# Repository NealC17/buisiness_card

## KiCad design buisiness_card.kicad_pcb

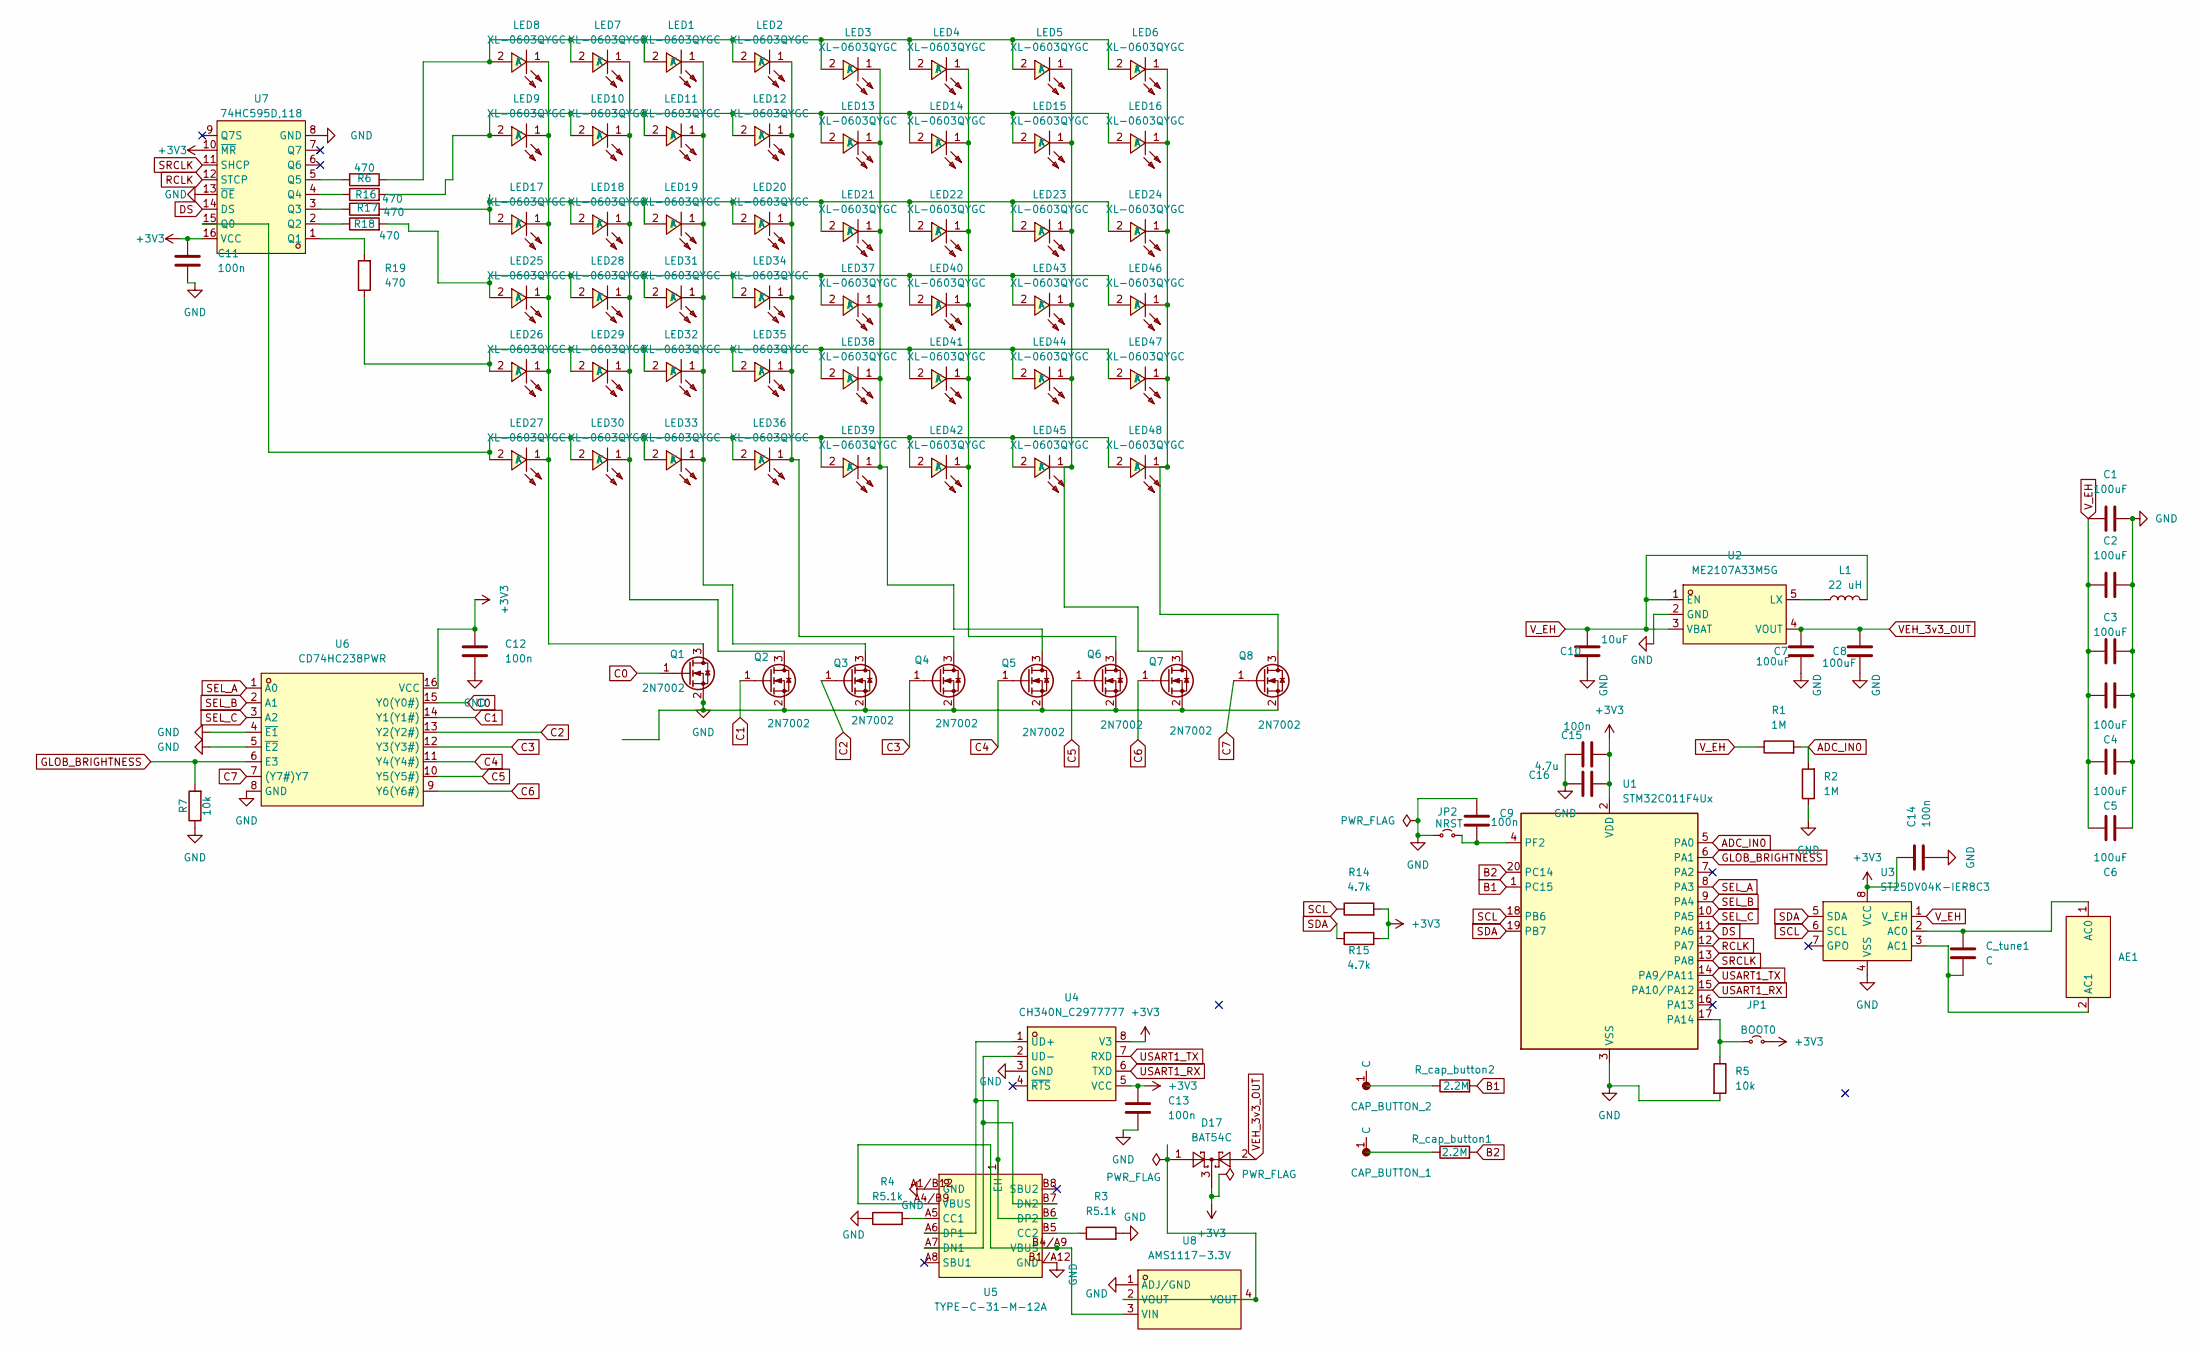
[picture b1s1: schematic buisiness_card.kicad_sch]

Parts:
AE1: NFC_NS12_OD31.5_NT12_TW0.3_SP0.325
C1, C2, C3, C4, C5, C6, C7, C8: 100uF; C_0603_1608Metric
C9: 100n; C_0603_1608Metric
C10: 10uF; C_0603_1608Metric
C11: 100n; C_0402_1005Metric_Pad0.74x0.62mm_HandSolder
C12, C13, C14, C15: 100n; C_0402_1005Metric
C16: 4.7u; C_0603_1608Metric
CAP_BUTTON_1, CAP_BUTTON_2: TestPoint_Pad_D4.0mm
C_tune1: C; C_0402_1005Metric
D17: BAT54C; SOT-23
JP1: BOOT0; SolderJumper-2_P1.3mm_Open_Pad1.0x1.5mm
JP2: NRST; SolderJumper-2_P1.3mm_Open_Pad1.0x1.5mm
L1: 22 uH; L_0603_1608Metric
LED1, LED2, LED3, LED4, LED5, LED6, LED7, LED8, LED9, LED10, LED11, LED12, LED13, LED14, LED15, LED16, LED17, LED18, LED19, LED20, LED21, LED22, LED23, LED24, LED25, LED26, LED27, LED28, LED29, LED30, LED31, LED32, LED33, LED34, LED35, LED36, LED37, LED38, LED39, LED40, LED41, LED42, LED43, LED44, LED45, LED46, LED47, LED48: XL-0603QYGC; LED0603-RD; MPN KT-0603YG; LCSC Part C2289
Q1, Q2, Q3, Q4, Q5, Q6, Q7, Q8: 2N7002; SOT-23
R1, R2: 1M; R_0402_1005Metric
R3, R4: R5.1k; R_0402_1005Metric
R5, R7: 10k; R_0402_1005Metric
R6, R16, R17, R18, R19: 470; R_0402_1005Metric
R14, R15: 4.7k; R_0402_1005Metric
R_cap_button1, R_cap_button2: 2.2M; R_0402_1005Metric
U1: STM32C011F4Ux; ST_UFQFPN-20_3x3mm_P0.5mm
U2: ME2107A33M5G; SOT-23-5_L2.9-W1.6-P0.95-LS2.8-BL; MPN ME2107A33M5G; LCSC Part C2681681
U3: ST25DV04K-IER8C3; DFN-8-1EP_3x2mm_P0.5mm_EP1.36x1.46mm
U4: CH340N_C2977777; SOP-8_L4.9-W3.9-P1.27-LS6.0-BL; MPN CH340N; LCSC Part C2977777
U5: TYPE-C-31-M-12A; USB-C-SMD_TYPE-C-31-M-12A; MPN TYPE-C-31-M-12A; LCSC Part C5337088
U6: CD74HC238PWR; TSSOP-16_L5.0-W4.4-P0.65-LS6.4-BL; MPN CD74HC238PWR; LCSC Part C403724
U7: 74HC595D,118; SOIC-16_L9.9-W3.9-P1.27-LS6.0-BL; MPN 74HC595D,118; LCSC Part C5947
U8: AMS1117-3.3V; SOT-223-4_L6.5-W3.5-P2.30-LS7.0-BR; MPN AMS1117-3.3V; LCSC Part C2688239

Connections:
+3V3: C11.1, C12.1, C13.1, C14.1, C15.2, C16.2, D17.3, JP1.2 (B), R14.2, R15.2, U1.2 (VDD), U3.8 (VCC), U4.5 (VCC), U4.8 (V3), U6.16 (VCC), U7.10 (~MR), U7.16 (VCC)
ADC_IN0: R1.2, R2.2, U1.5 (PA0)
B1: R_cap_button2.2, U1.1 (PC15)
B2: R_cap_button1.2, U1.20 (PC14)
C0: Q1.1 (G), U6.15 (Y0(Y0#))
C1: Q2.1 (G), U6.14 (Y1(Y1#))
C2: Q3.1 (G), U6.13 (Y2(Y2#))
C3: Q4.1 (G), U6.12 (Y3(Y3#))
C4: Q5.1 (G), U6.11 (Y4(Y4#))
C5: Q6.1 (G), U6.10 (Y5(Y5#))
C6: Q7.1 (G), U6.9 (Y6(Y6#))
C7: Q8.1 (G), U6.7 ((Y7#)Y7)
DS: U1.11 (PA6), U7.14 (DS)
GLOB_BRIGHTNESS: R7.2, U1.6 (PA1), U6.6 (E3)
GND: C1.2, C2.2, C3.2, C4.1, C5.1, C6.1, C7.2, C8.2, C9.1, C10.2, C11.2, C12.2, C13.2, C14.2, C15.1, C16.1, JP2.1 (A), Q1.2 (S), Q2.2 (S), Q3.2 (S), Q4.2 (S), Q5.2 (S), Q6.2 (S), Q7.2 (S), Q8.2 (S), R2.1, R3.2, R4.1, R5.2, R7.1, U1.3 (VSS), U2.2 (GND), U3.4 (VSS), U4.3 (GND), U5.A1/B12 (GND), U5.B1/A12 (GND), U6.4 (~E1), U6.5 (~E2), U6.8 (GND), U7.8 (GND), U7.13 (~OE), U8.1 (ADJ/GND)
unnamed: AE1.1 (AC0), C_tune1.1, U3.2 (AC0)
unnamed: AE1.2 (AC1), C_tune1.2, U3.3 (AC1)
unnamed: CAP_BUTTON_1.1 (C_1), R_cap_button1.1
unnamed: CAP_BUTTON_2.1 (C_1), R_cap_button2.1
unnamed: D17.1, U8.2 (VOUT), U8.4 (VOUT)
unnamed: JP1.1 (A), R5.1, U1.17 (PA14)
unnamed: C9.2, JP2.2 (B), U1.4 (PF2)
unnamed: LED1.2 (A), LED2.2 (A), LED3.2 (A), LED4.2 (A), LED5.2 (A), LED6.2 (A), LED7.2 (A), LED8.2 (A), R6.2
unnamed: LED1.1 (K), LED11.1 (K), LED19.1 (K), LED31.1 (K), LED32.1 (K), LED33.1 (K), Q3.3 (D)
unnamed: LED9.2 (A), LED10.2 (A), LED11.2 (A), LED12.2 (A), LED13.2 (A), LED14.2 (A), LED15.2 (A), LED16.2 (A), R16.2
unnamed: LED7.1 (K), LED10.1 (K), LED18.1 (K), LED28.1 (K), LED29.1 (K), LED30.1 (K), Q2.3 (D)
unnamed: LED2.1 (K), LED12.1 (K), LED20.1 (K), LED34.1 (K), LED35.1 (K), LED36.1 (K), Q4.3 (D)
unnamed: LED3.1 (K), LED13.1 (K), LED21.1 (K), LED37.1 (K), LED38.1 (K), LED39.1 (K), Q5.3 (D)
unnamed: LED4.1 (K), LED14.1 (K), LED22.1 (K), LED40.1 (K), LED41.1 (K), LED42.1 (K), Q6.3 (D)
unnamed: LED5.1 (K), LED15.1 (K), LED23.1 (K), LED43.1 (K), LED44.1 (K), LED45.1 (K), Q7.3 (D)
unnamed: LED6.1 (K), LED16.1 (K), LED24.1 (K), LED46.1 (K), LED47.1 (K), LED48.1 (K), Q8.3 (D)
unnamed: LED17.2 (A), LED18.2 (A), LED19.2 (A), LED20.2 (A), LED21.2 (A), LED22.2 (A), LED23.2 (A), LED24.2 (A), R17.2
unnamed: LED8.1 (K), LED9.1 (K), LED17.1 (K), LED25.1 (K), LED26.1 (K), LED27.1 (K), Q1.3 (D)
unnamed: LED25.2 (A), LED28.2 (A), LED31.2 (A), LED34.2 (A), LED37.2 (A), LED40.2 (A), LED43.2 (A), LED46.2 (A), R18.2
unnamed: LED26.2 (A), LED29.2 (A), LED32.2 (A), LED35.2 (A), LED38.2 (A), LED41.2 (A), LED44.2 (A), LED47.2 (A), R19.1
unnamed: LED27.2 (A), LED30.2 (A), LED33.2 (A), LED36.2 (A), LED39.2 (A), LED42.2 (A), LED45.2 (A), LED48.2 (A), U7.15 (Q0)
unnamed: L1.1, U2.5 (LX)
unnamed: U4.1 (UD+), U5.1 (EH), U5.A6 (DP1), U5.B6 (DP2)
unnamed: U4.2 (UD-), U5.A7 (DN1), U5.B7 (DN2)
unnamed: R4.2, U5.A5 (CC1)
unnamed: R3.1, U5.B5 (CC2)
unnamed: R19.2, U7.1 (Q1)
unnamed: R18.1, U7.2 (Q2)
unnamed: R17.1, U7.3 (Q3)
unnamed: R16.1, U7.4 (Q4)
unnamed: R6.1, U7.5 (Q5)
unnamed: U5.A4/B9 (VBUS), U5.B4/A9 (VBUS), U8.3 (VIN)
RCLK: U1.12 (PA7), U7.12 (STCP)
SCL: R14.1, U1.18 (PB6), U3.6 (SCL)
SDA: R15.1, U1.19 (PB7), U3.5 (SDA)
SEL_A: U1.8 (PA3), U6.1 (A0)
SEL_B: U1.9 (PA4), U6.2 (A1)
SEL_C: U1.10 (PA5), U6.3 (A2)
SRCLK: U1.13 (PA8), U7.11 (SHCP)
USART1_RX: U1.15 (PA10/PA12), U4.6 (TXD)
USART1_TX: U1.14 (PA9/PA11), U4.7 (RXD)
VEH_3v3_OUT: C7.1, C8.1, D17.2, U2.4 (VOUT)
V_EH: C1.1, C2.1, C3.1, C4.2, C5.2, C6.2, C10.1, L1.2, R1.1, U2.1 (EN), U2.3 (VBAT), U3.1 (V_EH)

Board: 2 copper layers, 103 parts (0 on the bottom side), 58 nets, no tracks yet.
